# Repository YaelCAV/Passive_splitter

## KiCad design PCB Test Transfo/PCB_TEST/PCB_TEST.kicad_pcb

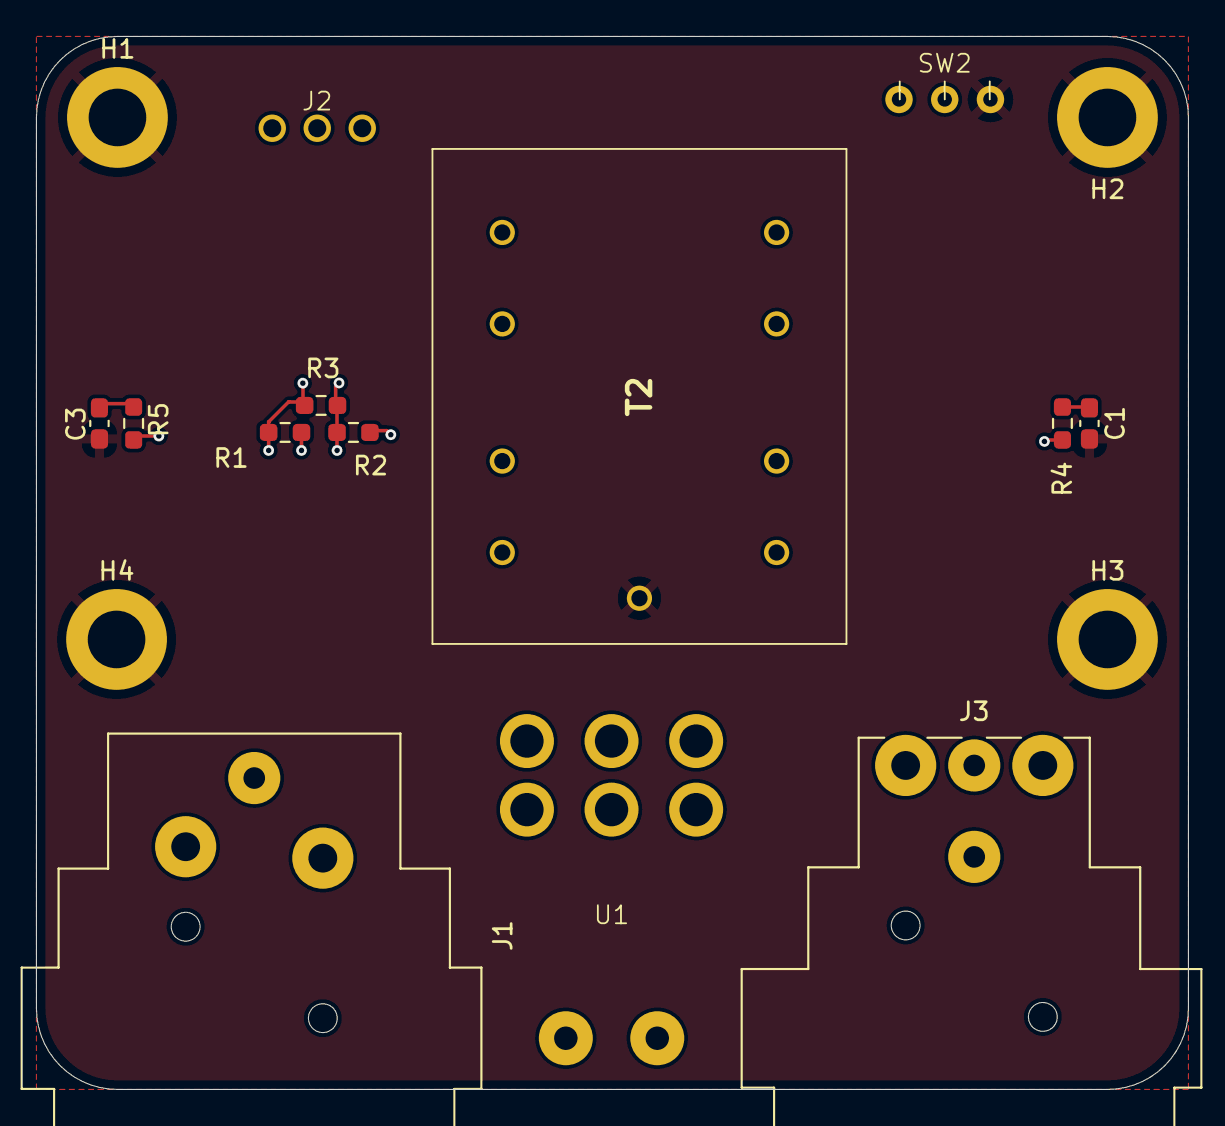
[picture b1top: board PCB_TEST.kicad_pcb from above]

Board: 4 copper layers, 64.0 x 58.5 mm, 17 parts (0 on the bottom side), 15 nets.

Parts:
C1, C3: 10u; C_0603_1608Metric_Pad1.08x0.95mm_HandSolder
H1, H2, H3, H4: MountingHole_Pad; MountingHole_3.2mm_M3_DIN965_Pad
J1: XLR3; Jack_XLR_Neutrik_NC3FAH1-0_Horizontal
J2: XLR3; 2.50 J connector wurth
J3: XLR3; Jack_XLR_Neutrik_NC3MAH_Horizontal
R1, R2: 5400; R_0603_1608Metric_Pad0.98x0.95mm_HandSolder
R3: 600; R_0603_1608Metric_Pad0.98x0.95mm_HandSolder
R4, R5: 51; R_0603_1608Metric_Pad0.98x0.95mm_HandSolder
SW2: SW_DPST_x2; switch wurth
T2: VTX-101-006; VTX101006
U1: WS-TOTV THT

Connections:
2: J2.2, R1.2, R3.2, T2.A1 (PRIMARY_2_1), U1.3
3: J2.3, R2.2, R3.1, T2.A4 (PRIMARY_1_2), U1.6
GND: C1.2, C3.2, H1.1, H2.1, H3.1, H4.1, SW2.3 (C), T2.SP1 (SCREEN)
Input1: J1.2, J2.1, R5.1
Input2: J1.1, U1.2
Input3: J1.3, U1.5
unnamed: C1.1, R4.2
unnamed: C3.1, R5.2
unnamed: R1.1, U1.1
unnamed: R2.1, U1.4
unnamed: T2.A2 (PRIMARY_1_1), T2.A3 (PRIMARY_2_2)
unnamed: T2.B2 (SECONDARY_2_1), T2.B3 (SECONDARY_1_2)
S1: J3.1, R4.1, SW2.1 (A)
S2: J3.2, T2.B1 (SECONDARY_1_1)
S3: J3.3, T2.B4 (SECONDARY_2_2)

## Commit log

2024-06-27 Create Hardware
2024-06-27 added kicad
